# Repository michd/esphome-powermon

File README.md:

# ESPHome Power Monitor

Device meant to monitor power usage of a house or circuit. Supports both blinking LED (e.g. 800 blinks per kWh consumed) with a detector, or interfacing with a Current Transformer (CT) clamp.

Fits an ESP32Devkit1 board. Please carefully compare the markings on the board with the ESP32 board.

See [Releases] for fabrication files. I generally order from [jlcpcb.com](https://jlcpcb.com), so that's what the files are tailored for.

## Hardware to bring yourself

- 2x Single row, 15 pin 2.54mm / 0.1" pitch PCB header sockets
- JST PH angled connectors, 2mm pitch:
  - 2 pin: For CT Clamp
  - 3 or 4 pin: For pulse detector
  - Cable assemblies to connect to these JST PH connectors
- Any other 2.54mm / 0.1" pitch connector up to 7 pins for other side of the board, if required
- Through-hole Burden resistor (see further down) Pitch: 7.62mm / 0.3", diameter: 2.5mm / ~0.1"
- For pulse meters: a pulse detector providing 3.3V logic level pulses

## Solderable jumpers

Some soldering is required to start using the board.

### PWR IN

The PWR IN jumper connectos the "Vin" connector pin either to the "Vin" pin of the ESP32 board, or to the 3.3V pin of same.

If you are supplying power via the connector (Vin and GND), select 3.3V or 5V depending on your power source.

If you are powering the ESP32 board directly via a USB cable, then you might use Vin the other way around. In that case the jumper selection can be used to decide whether to supply 3.3V or 5V _to_ that pin. In my case, I'm using this connector to feed a pulse detector 3.3V.

### A0 SRC

The board features a 4-channel analog to digital converter, the ADS1115IDGS. Its first input `A0` can be wired to the CT Clamp circuit, or to a connector on the other end of the board, `AI0`.

### A1-A3

The remaining ADC channels are also made available. 3 Jumpers are provided to make the connections to the ADC chip by the bottom of the board. If they are left unconnected, these pads can be used for other purposes. Note that all of these inputs should be kept within a 0-3.3V range.

## Pulsing meters

For using with a meter that blinks and LED or otherwise provides a pulse with every x amount of energy consumption, wire the pulse to "Blink" on the connector. It expects a 3.3V logic pulse, going directly to pin D27 on the ESP32.

## CT Clamps

Current Transformer clamps clip around a conductor carrying an alternating current and induce a smaller current themselves as a result.

See this introduction to using [CT Sensors](https://docs.openenergymonitor.org/electricity-monitoring/ct-sensors/introduction.html)

The important part is that you need to provide your own resistor to connect across the CT Clamp. Through ohm's law, the current through that resistor, multiplied by the resistance value results in a measurable voltage. This resistor is called the burden resistor and I'll talk more about it shortly.

### ADC bias calibration

Trimming potentiometer is used to set 50% midpoint at 1.65 V, to centre the CT Clamp signal around. Without a CT-Clamp connected, but with the board powered up, use a multimeter to measure the DC voltage from GND to the CT clamp pin furthest from the board edge. Tweak RV1 until this voltage is 1.65 V.

### Preselected burden resistor values

Use this table to select a resistor to use as burden resistor for your CT Clamp.

Info you'll need:

- $I_{live_{RMS}}$

  The maximum current you expect to go through the conductor you put the clamp around

- $n$

  Number of windings of the current transformer in the CT Clamp. For example: `100 A : 50mA` -> 2000

In the table, $R$ is the approximate ideal resistance value to get maximum range out of it, and E12/E24/E48 give a resistor value available in the [E-series of preferred numbers](https://en.wikipedia.org/wiki/E_series_of_preferred_numbers) - that is, a resistor you can actually buy.

|$I_{live_{RMS}}$|$n$|$R$|E12  | E24    | E48      |
|----:|---:|---------:|-------:|-------:|---------:|
|200 A|2000|   11.67 Ω| 10    Ω| 11    Ω|  11.5   Ω|
|100 A|2000|   23.33 Ω| 22    Ω| 22    Ω|  22.6   Ω|
| 60 A|2000|   38.89 Ω| 33    Ω| 36    Ω|  38.3   Ω|
| 50 A|2000|   46.67 Ω| 39    Ω| 43    Ω|  46.4   Ω|
| 32 A|2000|   72.92 Ω| 68    Ω| 68    Ω|  71.5   Ω|
| 16 A|2000|  145.84 Ω|120    Ω|130    Ω| 140     Ω|
| 10 A|2000|  233.35 Ω|220    Ω|220    Ω| 226     Ω|
|  5 A|2000|  466.69 Ω|390    Ω|430    Ω| 464     Ω|
|  2 A|2000|1,166.73 Ω|  1   kΩ|  1.1 kΩ|   1.15 kΩ|
|  1 A|2000|2,333.45 Ω|  2.2 kΩ|  2.2 kΩ|   2.26 kΩ|
|200 A|1000|    5.83 Ω|  5.6  Ω|  5.6  Ω|   5.62  Ω|
|100 A|1000|   11.67 Ω| 10    Ω| 11    Ω|  11.5   Ω|
| 60 A|1000|   19.45 Ω| 18    Ω| 18    Ω|  18.7   Ω|
| 50 A|1000|   23.33 Ω| 22    Ω| 22    Ω|  22.6   Ω|
| 32 A|1000|   36.46 Ω| 33    Ω| 36    Ω|  34.8   Ω|
| 16 A|1000|   72.92 Ω| 68    Ω| 68    Ω|  71.5   Ω|
| 10 A|1000|  116.67 Ω|100    Ω|110    Ω| 115     Ω|
|  5 A|1000|  233.35 Ω|220    Ω|220    Ω| 226     Ω|
|  2 A|1000|  583.36 Ω|560    Ω|560    Ω| 562     Ω|
|  1 A|1000|1,166.73 Ω|  1   kΩ|  1.1 kΩ|   1.15 kΩ|

### Selecting a burden resistor

These are more details about how this burden resistance is selected.

There are three factors at play to select the burden resistor.

- Desired output voltage range
- Maximum expected current through the live conductor the CT clamp clips around
- Number of windings of the current transformer (or, its ratio).

The last two combine into the maximum expected current through the current transformer winding and thus through the burden resistor.

#### Desired output voltage range: fixed

The desired output voltage range happens to be fixed. Based on the operating voltage of the ESP32 and the analog to digital converter (ADC) used in this design, the DC output voltage should never be higher than 3.3 V.

The voltage across the burden resistor will be in the form of a sine wave, so to remain between 0V and 3.3V, it is superimposed on a 1.65 V offset. From that, the peak voltage across the burden resistor ($V_{pk}$) should be **1.65 V**.

#### Maximum expected current through live conductor

To play it safe, this should probably match or exceed the current rating of the breaker on this circuit, or any lower-rated fuse that's in line with it.

For example, this could be 32 A.

#### Ratio of the current transformer

A CT Clamp will typically have a marking like `100 A : 50 mA` or something similar. Divide those by one another to get the ratio or number of windings. In this example that's

```math
n = \frac{100 A}{0.05 A} = 2000
```

#### Max expected current through burden resistor

Our max expected current through the burden resistor becomes the maximum expected current through the live conductor, divided by the number of windings. Taking our example:

```math
I_{burden_{rms}} = 32 A \div 2000 = 16 mA
```

This 32 A rating is typically an [RMS](https://en.wikipedia.org/wiki/Root_mean_square) value, that is, not the actual peak value. To get the peak value, multiply by $\sqrt2\$:

```math
I_{burden_{pk}} = 16 mA \times \sqrt{2} \approx 22.63 mA
```

#### Putting it all together

Now we can pick a burden resistance value:

```math
R_{burden} = V_{burden_{pk}} \div I_{burden_{pk}}

```

Example:

```math
R_{burden} = 1.65 V \div 22.63 mA \approx 72.91 \ohm
```

For convenience, here's the equation from base values:

```math
R_{burden} = V_{burden_{pk}} \div \frac{I_{live_{RMS}} \times \sqrt{2}}{n}
```

Where $V_{burden_{pk}} = 1.65V$.

You'll then want to pick a resistor that actually exists. Round the value down, since rounding up will result in higher voltages than those calculated.

## Playground and connections

All pins of the ESP32 have an additional open pad next to them to directly wire things to them as desired. All ADC inputs have a directly connected pad, near the center of the board (A0-A3). Each connector on the board has duplicate pads to wire directly to them.

Lastly, there is a "playground" area with 5 pads for the 5V*, 3.3V, and GND rails. A set of further pads, all spaced 2.54mm (0.1") apart is available as a sort of mini proto-board.These pads are not connected to anything unless marked otherwise on the board.

# ESPHome configuration

TODO.

Pertinent info if you already know what you're doing:

Pulse input pin: `27`

ADC:
  - domain: `ads1115`
  - i2c scl pin: `13`
  - i2c sda pin: `12`
  - i2c address: `0x48`
  - Multiplexers available:
    - `A0_GND` (CT Clamp or AI0)
    - `A1_GND`
    - `A2_GND`
    - `A3_GND`

Helpful esphome stuff:

- [CT Clamp](https://esphome.io/components/sensor/ct_clamp.html)
- [Pulse Meter Sensor](https://esphome.io/components/sensor/pulse_meter)
- [Custom Pulse Meter component by stevebaxter](https://community.home-assistant.io/t/how-to-count-pulse-frequency-accurately-with-esphome/201635/15) - This uses time between pulses to get a more precise idea of present power consumption

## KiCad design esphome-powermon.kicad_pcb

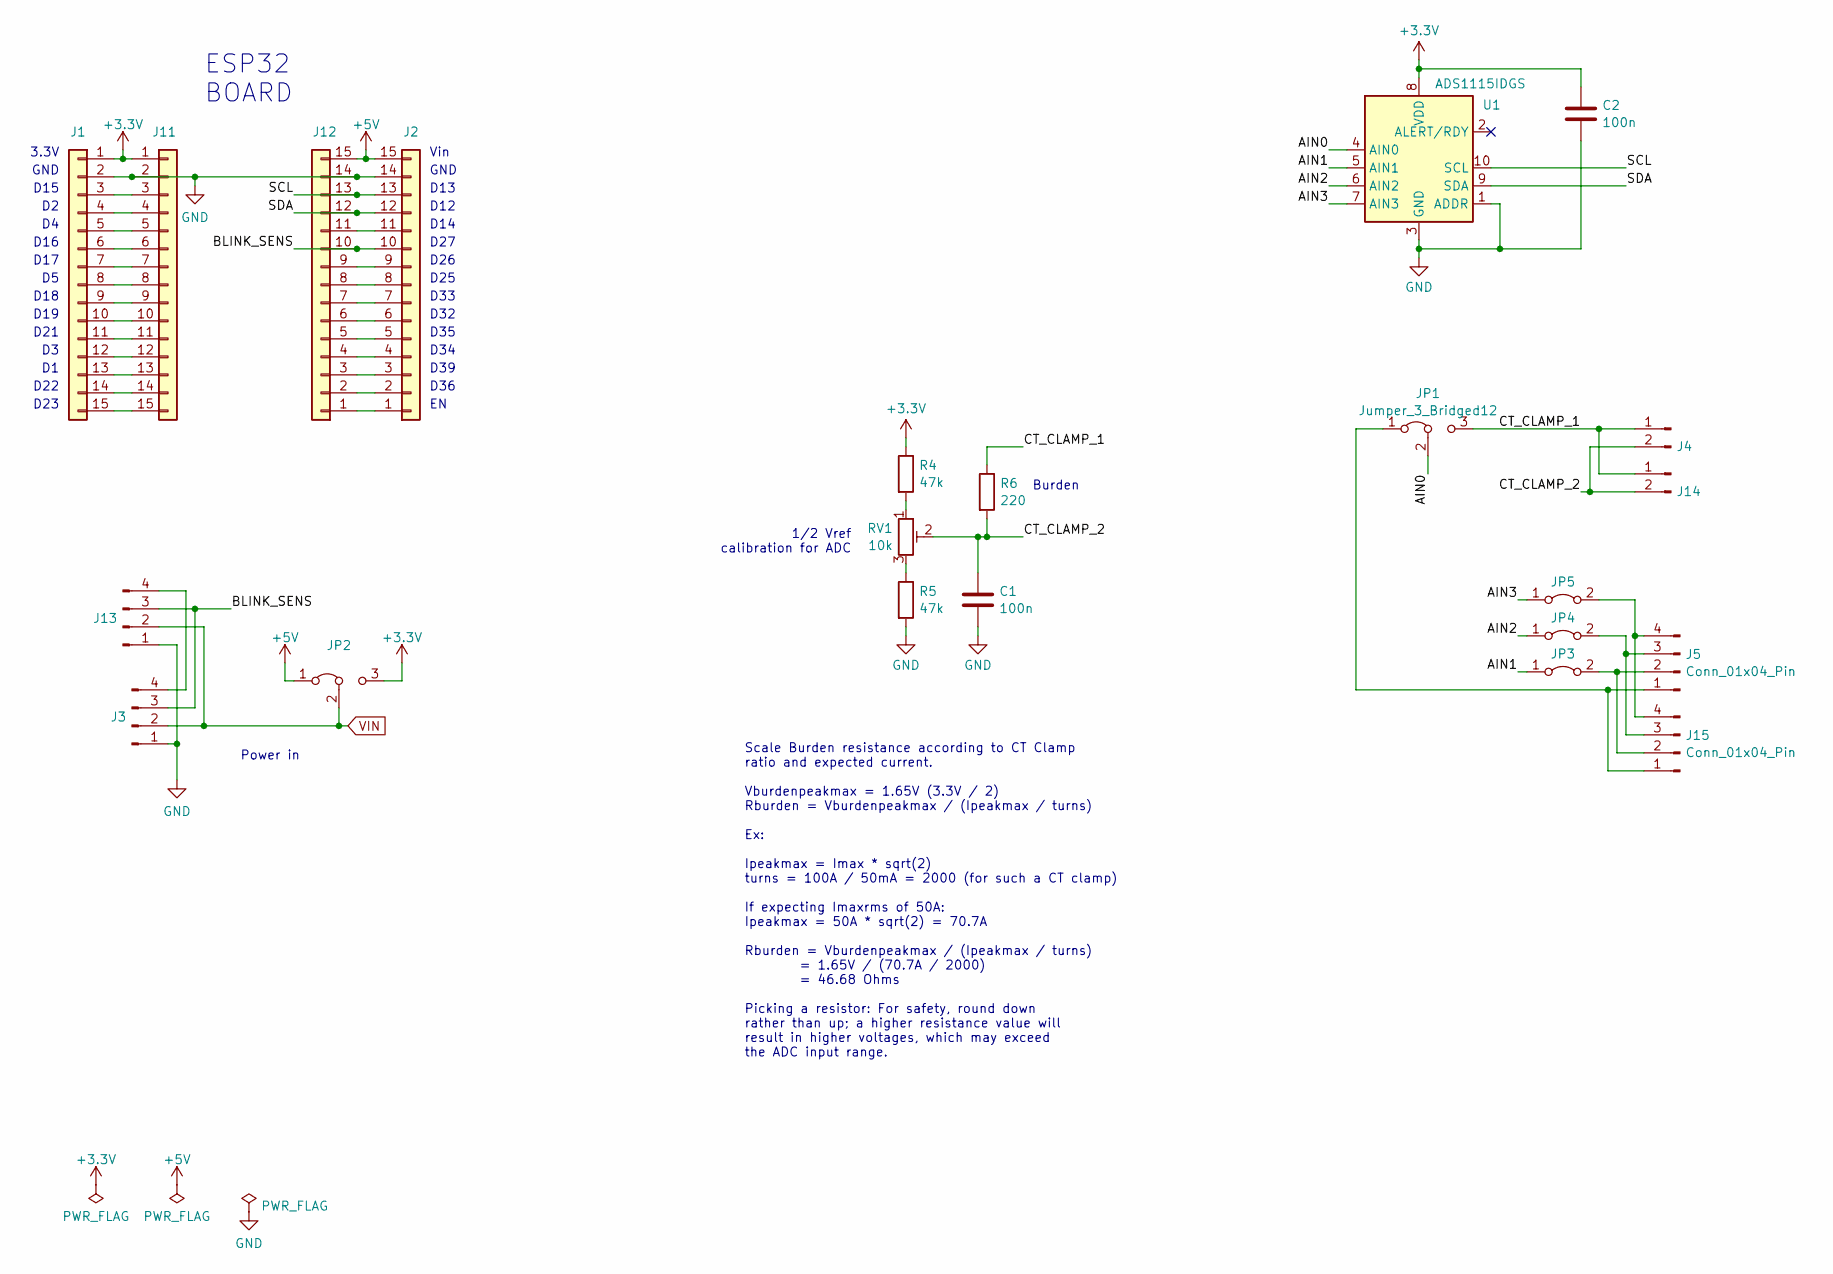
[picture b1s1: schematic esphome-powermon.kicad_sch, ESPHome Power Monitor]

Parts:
C1, C2: 100n; C_0603_1608Metric; LCSC C57112
J1, J2: Conn_01x15_Female; PinSocket_1x15_P2.54mm_Vertical
J3: Conn_01x04_Pin; JST_PH_S4B-PH-K_1x04_P2.00mm_Horizontal
J4: Conn_01x02_Pin; JST_PH_S2B-PH-K_1x02_P2.00mm_Horizontal
J5, J13, J15: Conn_01x04_Pin; PinHeader_1x04_P2.54mm_Vertical
J11, J12: Conn_01x15_Male; PinHeader_1x15_P2.54mm_Vertical
J14: Conn_01x02_Pin; PinHeader_1x02_P2.54mm_Vertical
JP1, JP2: Jumper_3_Bridged12; SolderJumper-3_P2.0mm_Open_TrianglePad1.0x1.5mm
JP3, JP4, JP5: Jumper_2_Bridged; SolderJumper-2_P1.3mm_Open_TrianglePad1.0x1.5mm
R4, R5: 47k; R_0603_1608Metric; LCSC C25819
R6: 220; R_Axial_DIN0207_L6.3mm_D2.5mm_P7.62mm_Horizontal
RV1: 10k; Potentiometer_Bourns_3313J_Vertical; LCSC C124616
U1: ADS1115IDGS; VSSOP-10_3x3mm_P0.5mm; LCSC C37593

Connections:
+3.3V: C2.1, J1.1, J11.1, JP2.3 (B), R4.1, U1.8 (VDD)
+5V: J2.15, J12.15, JP2.1 (A)
/AIN0: JP1.2 (C), U1.4 (AIN0)
/AIN1: JP3.1 (A), U1.5 (AIN1)
/AIN2: JP4.1 (A), U1.6 (AIN2)
/AIN3: JP5.1 (A), U1.7 (AIN3)
/BLINK_SENS: J2.10, J3.3, J12.10, J13.3
/CT_CLAMP_1: J4.1, J14.1, JP1.3 (B), R6.1
/CT_CLAMP_2: C1.1, J4.2, J14.2, R6.2, RV1.2
/SCL: J2.13, J12.13, U1.10 (SCL)
/SDA: J2.12, J12.12, U1.9 (SDA)
GND: C1.2, C2.2, J1.2, J2.14, J3.1, J11.2, J12.14, J13.1, R5.2, U1.1 (ADDR), U1.3 (GND)
unnamed: J1.3, J11.3
unnamed: J1.4, J11.4
unnamed: J1.5, J11.5
unnamed: J1.6, J11.6
unnamed: J1.7, J11.7
unnamed: J1.8, J11.8
unnamed: J1.9, J11.9
unnamed: J1.10, J11.10
unnamed: J1.11, J11.11
unnamed: J1.12, J11.12
unnamed: J1.13, J11.13
unnamed: J1.14, J11.14
unnamed: J1.15, J11.15
unnamed: J2.1, J12.1
unnamed: J2.2, J12.2
unnamed: J2.3, J12.3
unnamed: J2.4, J12.4
unnamed: J2.5, J12.5
unnamed: J2.6, J12.6
unnamed: J2.7, J12.7
unnamed: J2.8, J12.8
unnamed: J2.9, J12.9
unnamed: J2.11, J12.11
unnamed: J3.4, J13.4
unnamed: J5.1, J15.1, JP1.1 (A)
unnamed: J5.2, J15.2, JP3.2 (B)
unnamed: J5.3, J15.3, JP4.2 (B)
unnamed: J5.4, J15.4, JP5.2 (B)
unnamed: R4.2, RV1.1
unnamed: R5.1, RV1.3
VIN: J3.2, J13.2, JP2.2 (C)

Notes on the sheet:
D15
D33
Vin
Burden
D22
Power in
D14
D12
D26
D35
D36
D23
D18
D27
1/2 Vref calibration for ADC
D32
D39
D13
D25
D19
D34
D21
3.3V
Scale Burden resistance according to CT Clamp ratio and expected current. Vburdenpeakmax = 1.65V (3.3V / 2) Rburden = Vburdenpeakmax / (Ipeakmax / turns) Ex: Ipeakmax = Imax * sqrt(2) turns = 100A / 50mA = 2000 (for such a CT clamp) If expecting Imaxrms of 50A: Ipeakmax = 50A * sqrt(2) = 70.7A Rbur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
ESP32 BOARD
D16
GND
D17

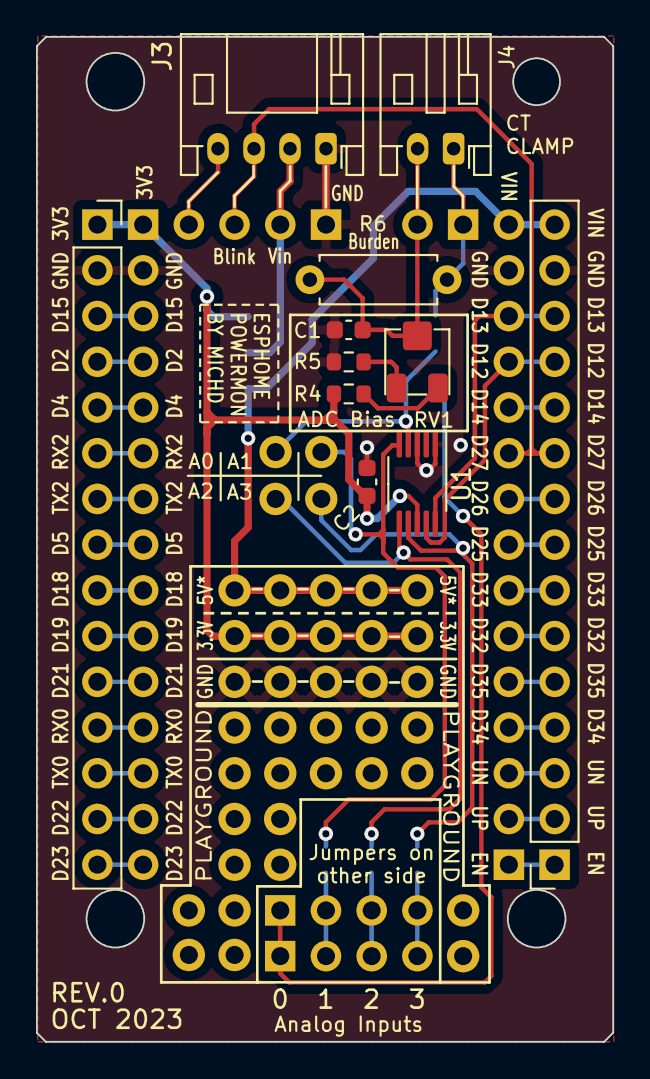
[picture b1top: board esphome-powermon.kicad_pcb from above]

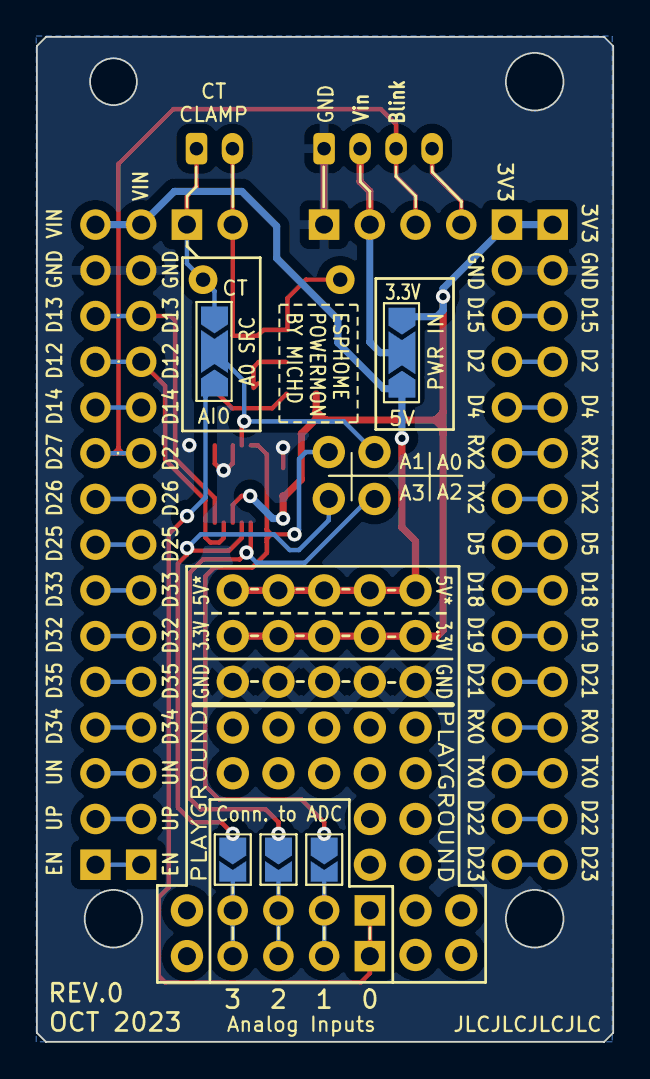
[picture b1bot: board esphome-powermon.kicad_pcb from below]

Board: 2 copper layers, 32.0 x 55.8 mm, 22 parts (5 on the bottom side), 43 nets.

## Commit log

2023-10-07 Initial commit, rev0 of board
2023-10-08 Replace burden resistor with TH footprint
    Still for rev0.
2023-10-08 Add README docs
2023-10-08 Correct page markings
2023-10-08 Couple of readme fixes
